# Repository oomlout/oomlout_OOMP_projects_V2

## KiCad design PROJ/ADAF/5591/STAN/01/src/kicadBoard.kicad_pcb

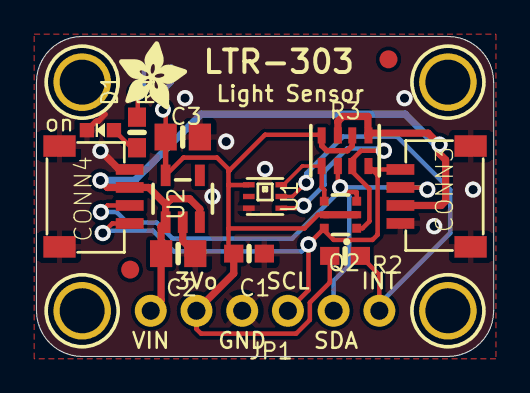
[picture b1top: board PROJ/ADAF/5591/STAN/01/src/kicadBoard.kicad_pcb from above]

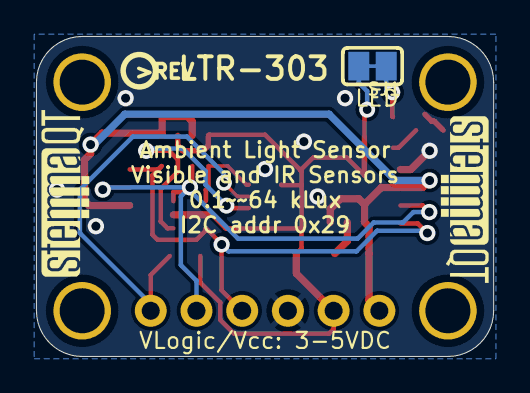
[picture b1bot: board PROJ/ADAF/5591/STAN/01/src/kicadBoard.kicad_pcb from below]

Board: 2 copper layers, 25.4 x 17.8 mm, 24 parts (4 on the bottom side), 10 nets.

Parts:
C1: 0.1uF; 0603-NO
C2, C3: 10uF; 0805-NO
CONN3, CONN4: STEMMA_I2C_QT; JST_SH4
D1: GREEN; CHIPLED_0603_NOOUTLINE
FID3, FID4: FIDUCIAL_1MM
JP1: 1X06_ROUND_70
Q2: BSS138; SOT363
R1, R2: 10K; 0603-NO
R3: 10K Pack; RESPACK_4X0603
SJ1: SOLDERJUMPER_CLOSEDWIRE
U1: LTR_303; LTR390
U2: AP2127K-3.3; SOT23-5
U$1, U$17, U$19, U$21: MOUNTINGHOLE2.5; MOUNTINGHOLE_2.5_PLATED
U$22: ADAFRUIT_3.5MM
U$25: PCBFEAT-REV-040
U$30, U$31: STEMMAQT

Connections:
3.3V: C1.1, C3.1, JP1.2, Q2.2, Q2.5, R2.1, R3.2, R3.4, SJ1.2, U1.1, U2.5
GND: C1.2, C2.2, C3.2, CONN3.1, CONN3.MT1, CONN3.MT2, CONN4.1, CONN4.MT1, CONN4.MT2, D1.C, JP1.3, U1.3, U2.2
INT: JP1.6, R2.2, U1.5
unnamed: D1.A, R1.2
unnamed: R1.1, SJ1.1
SCL: CONN3.4, CONN4.4, JP1.4, Q2.6, R3.8
SCL_3V: Q2.1, R3.7, U1.4
SDA: CONN3.3, CONN4.3, JP1.5, Q2.3, R3.6
SDA_3V: Q2.4, R3.5, U1.6
VCC: C2.1, CONN3.2, CONN4.2, JP1.1, R3.1, R3.3, U2.1, U2.3

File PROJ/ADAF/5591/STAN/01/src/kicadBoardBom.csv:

"Id";"Designator";"Package";"Quantity";"Designation";"Supplier and ref";
1;"JP1";"1X06_ROUND_70";1;"";;;
2;"C1";"0603-NO";1;"0.1uF";;;
3;"C3,C2";"0805-NO";2;"10uF";;;
4;"D1";"CHIPLED_0603_NOOUTLINE";1;"GREEN";;;
5;"FID4,FID3";"FIDUCIAL_1MM";2;"FIDUCIAL_1MM";;;
6;"U2";"SOT23-5";1;"AP2127K-3.3";;;
7;"U$17,U$21,U$1,U$19";"MOUNTINGHOLE_2.5_PLATED";4;"MOUNTINGHOLE2.5";;;
8;"Q2";"SOT363";1;"BSS138";;;
9;"CONN3,CONN4";"JST_SH4";2;"STEMMA_I2C_QT";;;
10;"R2,R1";"0603-NO";2;"10K";;;
11;"R3";"RESPACK_4X0603";1;"10K Pack";;;
12;"U1";"LTR390";1;"LTR_303";;;
13;"U$22";"ADAFRUIT_3.5MM";1;"";;;
14;"U$30,U$31";"STEMMAQT";2;"";;;
15;"U$25";"PCBFEAT-REV-040";1;"";;;
16;"SJ1";"SOLDERJUMPER_CLOSEDWIRE";1;"";;;

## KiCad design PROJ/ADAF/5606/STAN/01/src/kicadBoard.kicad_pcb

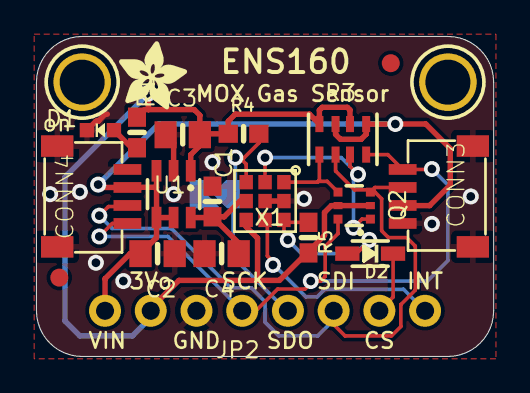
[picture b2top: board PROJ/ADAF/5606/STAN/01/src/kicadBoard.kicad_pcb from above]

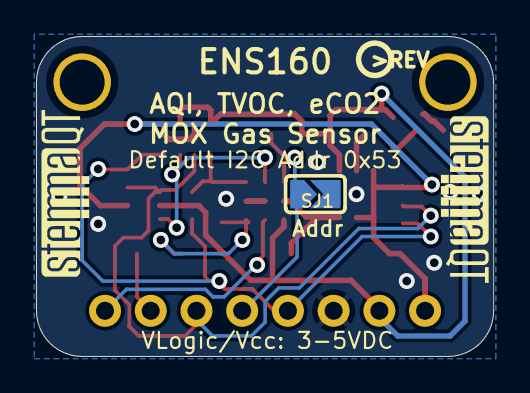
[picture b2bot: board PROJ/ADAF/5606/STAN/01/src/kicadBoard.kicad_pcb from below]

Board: 2 copper layers, 25.4 x 17.8 mm, 25 parts (4 on the bottom side), 13 nets.

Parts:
C1: 0.1uF; 0603-NO
C2, C3, C4: 10uF; 0805-NO
CONN3, CONN4: STEMMA_I2C_QT; JST_SH4
D1: GREEN; CHIPLED_0603_NOOUTLINE
D2: 1N4148; SOD-323
FID3, FID4: FIDUCIAL_1MM
JP2: 1X08_ROUND_70
Q2: BSS138; SOT363
R1, R4, R5: 10K; 0603-NO
R3: 10K pack; RESPACK_4X0603
SJ1: SOLDERJUMPER_ARROW_NOPASTE
U1: AP7312-1833; SOT23-6
U$1, U$17: MOUNTINGHOLE2.5; MOUNTINGHOLE_2.5_PLATED
U$20: ADAFRUIT_3.5MM
U$25: PCBFEAT-REV-040
U$30, U$31: STEMMAQT
X1: ENS160

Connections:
1.8V: C1.1, C4.1, U1.6, X1.4
3.3V: C3.1, JP2.2, Q2.2, Q2.5, R1.1, R3.2, R3.4, R4.2, R5.2, U1.1, X1.5
CS_3V: D2.A, R5.1, X1.7
GND: C1.2, C2.2, C3.2, C4.2, CONN3.1, CONN3.MT1, CONN3.MT2, CONN4.1, CONN4.MT1, CONN4.MT2, D1.C, JP2.3, SJ1.2, U1.2, X1.8, X1.9
unnamed: D1.A, R1.2
SCL/SCK: CONN3.4, CONN4.4, JP2.4, Q2.6, R3.8
SCL_3V: Q2.1, R3.7, X1.2
SDA/MOSI: CONN3.3, CONN4.3, JP2.6, Q2.3, R3.6
SDA_3V: Q2.4, R3.5, X1.1
SDO/ADR: JP2.5, R4.1, SJ1.1, X1.3
VCC: C2.1, CONN3.2, CONN4.2, JP2.1, R3.1, R3.3, U1.3, U1.4, U1.5
~CS: D2.C, JP2.7
~INT: JP2.8, X1.6

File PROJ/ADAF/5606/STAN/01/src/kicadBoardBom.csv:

"Id";"Designator";"Package";"Quantity";"Designation";"Supplier and ref";
1;"CONN3,CONN4";"JST_SH4";2;"STEMMA_I2C_QT";;;
2;"C4,C3,C2";"0805-NO";3;"10uF";;;
3;"R3";"RESPACK_4X0603";1;"10K pack";;;
4;"R4,R1,R5";"0603-NO";3;"10K";;;
5;"FID4,FID3";"FIDUCIAL_1MM";2;"FIDUCIAL_1MM";;;
6;"U1";"SOT23-6";1;"AP7312-1833";;;
7;"X1";"ENS160";1;"ENS160";;;
8;"D2";"SOD-323";1;"1N4148";;;
9;"D1";"CHIPLED_0603_NOOUTLINE";1;"GREEN";;;
10;"U$20";"ADAFRUIT_3.5MM";1;"";;;
11;"Q2";"SOT363";1;"BSS138";;;
12;"JP2";"1X08_ROUND_70";1;"";;;
13;"C1";"0603-NO";1;"0.1uF";;;
14;"U$17,U$1";"MOUNTINGHOLE_2.5_PLATED";2;"MOUNTINGHOLE2.5";;;
15;"U$25";"PCBFEAT-REV-040";1;"";;;
16;"SJ1";"SOLDERJUMPER_ARROW_NOPASTE";1;"";;;
17;"U$30,U$31";"STEMMAQT";2;"";;;

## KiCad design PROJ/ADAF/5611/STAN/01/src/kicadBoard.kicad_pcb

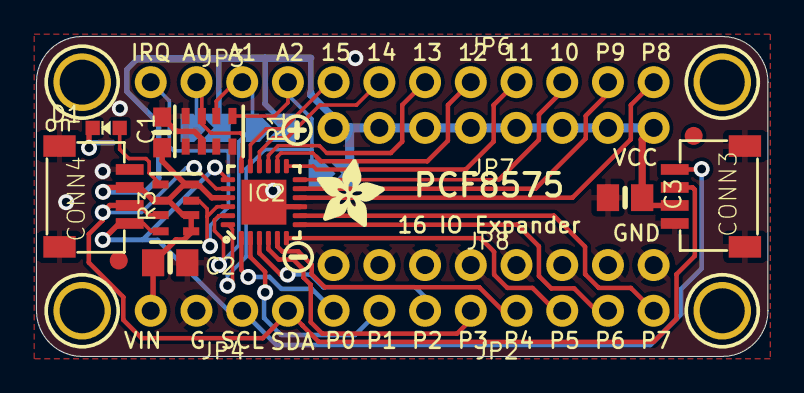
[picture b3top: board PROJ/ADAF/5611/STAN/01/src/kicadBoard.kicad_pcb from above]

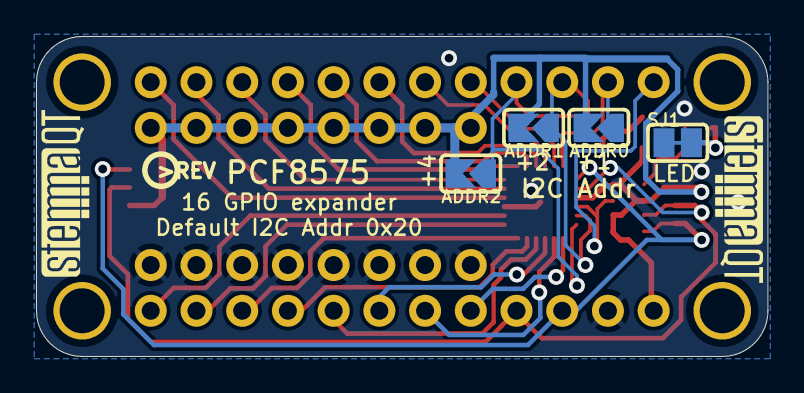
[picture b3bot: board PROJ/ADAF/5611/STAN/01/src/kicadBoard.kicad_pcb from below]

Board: 2 copper layers, 40.6 x 17.8 mm, 31 parts (7 on the bottom side), 26 nets.

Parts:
ADDR0, ADDR1, ADDR2: SOLDERJUMPER_ARROW_NOPASTE
C1: 0.1uF; 0603-NO
C2, C3: 10uF; 0805-NO
CONN3, CONN4: STEMMA_I2C_QT; JST_SH4
D1: GREEN; CHIPLED_0603_NOOUTLINE
FID3, FID4: FIDUCIAL_1MM
IC2: PCF8575; QFN24_4MM_SMSC
JP2, JP6, JP7, JP8: 1X08_ROUND_70
JP3, JP4: 1X04_ROUND
R1, R3: 10K Pack; RESPACK_4X0603
SJ1: SOLDERJUMPER_CLOSEDWIRE
U$1, U$17, U$19, U$21: MOUNTINGHOLE2.5; MOUNTINGHOLE_2.5_PLATED
U$2: SYMBOL_PLUS
U$3: SYMBOL_MINUS
U$22: ADAFRUIT_3.5MM
U$25: PCBFEAT-REV-040
U$30, U$31: STEMMAQT

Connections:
A0: ADDR0.1, IC2.18, JP3.2, R1.7
A1: ADDR1.1, IC2.23, JP3.3, R1.6
A2: ADDR2.1, IC2.24, JP3.4, R1.5
GND: C1.2, C2.2, C3.2, CONN3.1, CONN3.MT1, CONN3.MT2, CONN4.1, CONN4.MT1, CONN4.MT2, IC2.9, IC2.THERM, JP4.2, JP8.1, JP8.2, JP8.3, JP8.4, JP8.5, JP8.6, JP8.7, JP8.8, R1.1, R1.2, R1.3, R1.4, R1.8, SJ1.1
GPA0: IC2.1, JP2.1
GPA1: IC2.2, JP2.2
GPA2: IC2.3, JP2.3
GPA3: IC2.4, JP2.4
GPA4: IC2.5, JP2.5
GPA5: IC2.6, JP2.6
GPA6: IC2.7, JP2.7
GPA7: IC2.8, JP2.8
GPB0: IC2.10, JP6.1
GPB1: IC2.11, JP6.2
GPB2: IC2.12, JP6.3
GPB3: IC2.13, JP6.4
GPB4: IC2.14, JP6.5
GPB5: IC2.15, JP6.6
GPB6: IC2.16, JP6.7
GPB7: IC2.17, JP6.8
INTA: IC2.22, JP3.1, R3.3
unnamed: D1.A, R3.5
unnamed: D1.C, SJ1.2
SCL: CONN3.4, CONN4.4, IC2.19, JP4.3, R3.8
SDA: CONN3.3, CONN4.3, IC2.20, JP4.4, R3.7
VCC: ADDR0.2, ADDR1.2, ADDR2.2, C1.1, C2.1, C3.1, CONN3.2, CONN4.2, IC2.21, JP4.1, JP7.1, JP7.2, JP7.3, JP7.4, JP7.5, JP7.6, JP7.7, JP7.8, R3.1, R3.2, R3.4, R3.6

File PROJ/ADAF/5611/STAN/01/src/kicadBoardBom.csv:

"Id";"Designator";"Package";"Quantity";"Designation";"Supplier and ref";
1;"CONN4,CONN3";"JST_SH4";2;"STEMMA_I2C_QT";;;
2;"IC2";"QFN24_4MM_SMSC";1;"PCF8575";;;
3;"C2,C3";"0805-NO";2;"10uF";;;
4;"JP8,JP6,JP2,JP7";"1X08_ROUND_70";4;"";;;
5;"U$3";"SYMBOL_MINUS";1;"";;;
6;"D1";"CHIPLED_0603_NOOUTLINE";1;"GREEN";;;
7;"FID4,FID3";"FIDUCIAL_1MM";2;"FIDUCIAL_1MM";;;
8;"U$22";"ADAFRUIT_3.5MM";1;"";;;
9;"U$2";"SYMBOL_PLUS";1;"";;;
10;"R3,R1";"RESPACK_4X0603";2;"10K Pack";;;
11;"U$17,U$21,U$19,U$1";"MOUNTINGHOLE_2.5_PLATED";4;"MOUNTINGHOLE2.5";;;
12;"C1";"0603-NO";1;"0.1uF";;;
13;"JP4,JP3";"1X04_ROUND";2;"";;;
14;"U$31,U$30";"STEMMAQT";2;"";;;
15;"ADDR0,ADDR2,ADDR1";"SOLDERJUMPER_ARROW_NOPASTE";3;"";;;
16;"U$25";"PCBFEAT-REV-040";1;"";;;
17;"SJ1";"SOLDERJUMPER_CLOSEDWIRE";1;"";;;

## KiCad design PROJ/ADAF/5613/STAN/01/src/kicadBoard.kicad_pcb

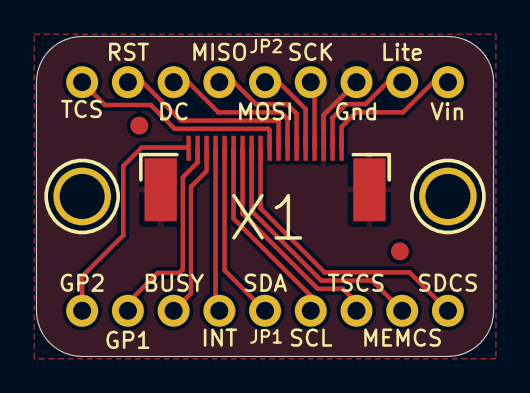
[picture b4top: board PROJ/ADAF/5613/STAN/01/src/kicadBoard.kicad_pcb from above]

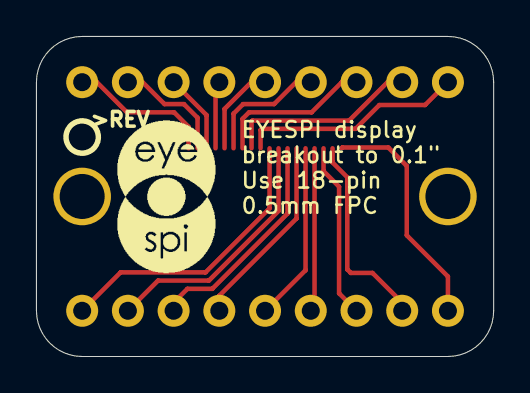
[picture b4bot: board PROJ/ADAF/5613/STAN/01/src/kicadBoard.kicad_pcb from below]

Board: 16 copper layers, 25.4 x 17.8 mm, 9 parts (2 on the bottom side), 18 nets.

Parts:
JP1, JP2: 1X09_ROUND_70
U$2: PCBFEAT-REV-040
U$4, U$5: FIDUCIAL_1MM
U$9, U$10: MOUNTINGHOLE2.5; MOUNTINGHOLE_2.5_PLATED
U$22: EYESPI_MINI_LOGO
X1: EYE_SPI_DISPLAY_FLIP; EYE_SPI_DISPLAY_BOTCONTACT

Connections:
BUSY: JP1.7, X1.16
CARDCS: JP1.1, X1.10
GND: JP2.3, X1.3, X1.SUPPORT1, X1.SUPPORT2
GPIO1: JP1.8, X1.17
GPIO2: JP1.9, X1.18
INT: JP1.6, X1.15
LITE: JP2.2, X1.2
MEM_CS: JP1.2, X1.11
MISO: JP2.6, X1.6
MOSI: JP2.5, X1.5
SCK: JP2.4, X1.4
SCL: JP1.4, X1.13
SDA: JP1.5, X1.14
TFTCS: JP2.9, X1.9
TFTDC: JP2.7, X1.7
TFTRST: JP2.8, X1.8
TSCS: JP1.3, X1.12
VIN: JP2.1, X1.1

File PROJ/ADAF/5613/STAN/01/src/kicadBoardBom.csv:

"Id";"Designator";"Package";"Quantity";"Designation";"Supplier and ref";
1;"U$9,U$10";"MOUNTINGHOLE_2.5_PLATED";2;"MOUNTINGHOLE2.5";;;
2;"U$5,U$4";"FIDUCIAL_1MM";2;"FIDUCIAL_1MM";;;
3;"JP2,JP1";"1X09_ROUND_70";2;"";;;
4;"X1";"EYE_SPI_DISPLAY_BOTCONTACT";1;"EYE_SPI_DISPLAY_FLIP";;;
5;"U$22";"EYESPI_MINI_LOGO";1;"";;;
6;"U$2";"PCBFEAT-REV-040";1;"";;;

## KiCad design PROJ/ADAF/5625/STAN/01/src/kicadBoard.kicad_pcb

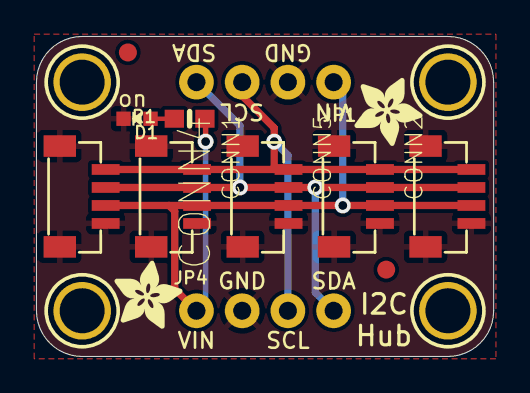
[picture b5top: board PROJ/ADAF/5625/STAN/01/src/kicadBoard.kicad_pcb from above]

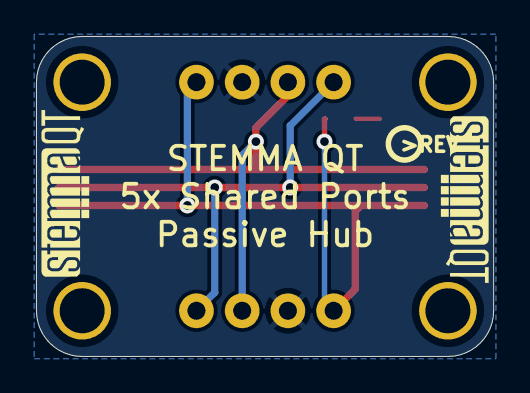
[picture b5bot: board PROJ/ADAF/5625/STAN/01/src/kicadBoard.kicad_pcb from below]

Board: 2 copper layers, 25.4 x 17.8 mm, 20 parts (3 on the bottom side), 5 nets.

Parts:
CONN1, CONN2, CONN3, CONN4, CONN5: STEMMA_I2C_QTRA; JST_SH4_RA
D1: GREEN; CHIPLED_0603_NOOUTLINE
FID3, FID4: FIDUCIAL_1MM
JP1, JP4: 1X04_ROUND_76
R1: 10K; 0603-NO
U$1, U$17, U$19, U$21: MOUNTINGHOLE2.5; MOUNTINGHOLE_2.5_PLATED
U$2, U$3: ADAFRUIT_3.5MM
U$25: PCBFEAT-REV-040
U$30, U$31: STEMMAQT

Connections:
GND: CONN1.1, CONN1.MT1, CONN1.MT2, CONN2.1, CONN2.MT1, CONN2.MT2, CONN3.1, CONN3.MT1, CONN3.MT2, CONN4.1, CONN4.MT1, CONN4.MT2, CONN5.1, CONN5.MT1, CONN5.MT2, D1.C, JP1.2, JP4.2
unnamed: D1.A, R1.2
SCL: CONN1.4, CONN2.4, CONN3.4, CONN4.4, CONN5.4, JP1.3, JP4.3
SDA: CONN1.3, CONN2.3, CONN3.3, CONN4.3, CONN5.3, JP1.4, JP4.4
VCC: CONN1.2, CONN2.2, CONN3.2, CONN4.2, CONN5.2, JP1.1, JP4.1, R1.1

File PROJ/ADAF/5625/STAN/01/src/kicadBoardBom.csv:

"Id";"Designator";"Package";"Quantity";"Designation";"Supplier and ref";
1;"CONN2,CONN3,CONN1,CONN4,CONN5";"JST_SH4_RA";5;"STEMMA_I2C_QTRA";;;
2;"D1";"CHIPLED_0603_NOOUTLINE";1;"GREEN";;;
3;"FID4,FID3";"FIDUCIAL_1MM";2;"FIDUCIAL_1MM";;;
4;"U$17,U$21,U$19,U$1";"MOUNTINGHOLE_2.5_PLATED";4;"MOUNTINGHOLE2.5";;;
5;"U$3,U$2";"ADAFRUIT_3.5MM";2;"";;;
6;"JP1,JP4";"1X04_ROUND_76";2;"";;;
7;"R1";"0603-NO";1;"10K";;;
8;"U$30,U$31";"STEMMAQT";2;"";;;
9;"U$25";"PCBFEAT-REV-040";1;"";;;

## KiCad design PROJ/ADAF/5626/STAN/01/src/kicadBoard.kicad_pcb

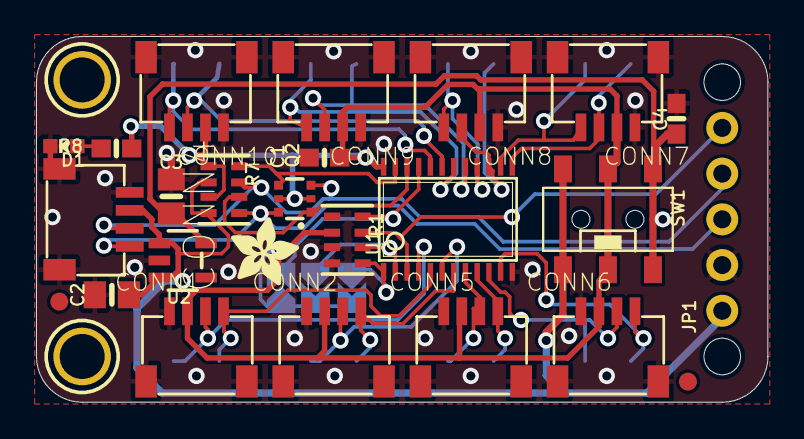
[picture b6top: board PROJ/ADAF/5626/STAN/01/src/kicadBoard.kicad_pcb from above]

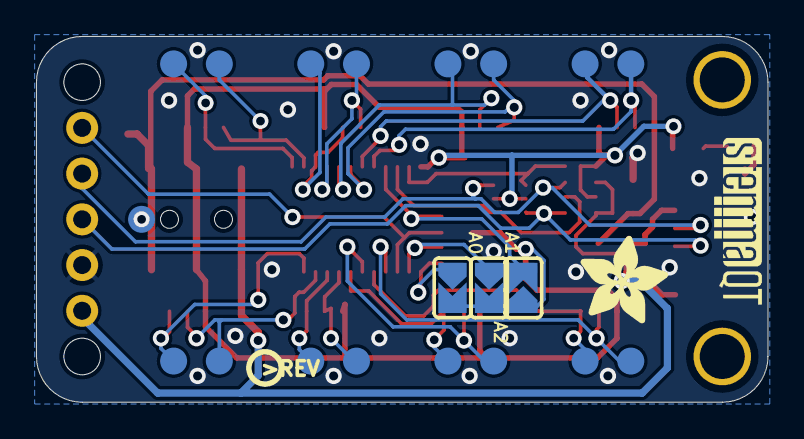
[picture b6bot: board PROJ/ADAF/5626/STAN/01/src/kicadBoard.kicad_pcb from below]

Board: 2 copper layers, 40.6 x 20.3 mm, 77 parts (28 on the bottom side), 29 nets.

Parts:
@HOLE0, @HOLE1: (no value)
A0, A1, A2: SOLDERJUMPER_ARROW_NOPASTE
C1: 1uF; 0603-NO
C2, C3: 10uF; 0805-NO
C4: 0.1uF; 0603-NO
CONN1, CONN2, CONN4, CONN5, CONN6, CONN7, CONN8, CONN9, CONN10: STEMMA_I2C_QT; JST_SH4
D1: GREEN; CHIPLED_0603_NOOUTLINE
FID2, FID4: FIDUCIAL_1MM
JP1: 1X05_ROUND_70
PLABEL0: PLABEL0
PLABEL1: PLABEL1
PLABEL2: PLABEL2
PLABEL3: PLABEL3
PLABEL4: PLABEL4
PLABEL5: PLABEL5
PLABEL6: PLABEL6
PLABEL7: PLABEL7
PLABEL8: PLABEL8
PLABEL9: PLABEL9
PLABEL10: PLABEL10
PLABEL11: PLABEL11
PLABEL12: PLABEL12
PLABEL13: PLABEL13
PLABEL14: PLABEL14
PLABEL15: PLABEL15
PLABEL16: PLABEL16
PLABEL17: PLABEL17
PLABEL18: PLABEL18
PLABEL19: PLABEL19
PLABEL20: PLABEL20
PLABEL21: PLABEL21
PLABEL22: PLABEL22
PLABEL23: PLABEL23
PLABEL24: PLABEL24
Q2: BSS138; SOT363
R1, R7: 10K Pack; RESPACK_4X0603
R8: 10K; 0603-NO
SW1: AYZ0202AGRLC; EG1390
TP1, TP2, TP3, TP4, TP5, TP6, TP7, TP8, TP9, TP10, TP11, TP12, TP13, TP14, TP15, TP16, TP17: TESTPOINT_ROUND_1.5MM_NO
U1: xCA9548APWR; TSSOP24
U2: AP2112K-3.3; SOT23-5
U$5: ADAFRUIT_5MM
U$19, U$22: MOUNTINGHOLE2.5; MOUNTINGHOLE_2.5_PLATED
U$28: ADAFRUIT_3.5MM
U$29: PCBFEAT-REV-040
U$31: STEMMAQT

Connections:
0SCL: CONN1.4, TP15.P$1, U1.5
0SDA: CONN1.3, TP16.P$1, U1.4
1SCL: CONN2.4, TP13.P$1, U1.7
1SDA: CONN2.3, TP14.P$1, U1.6
2SCL: CONN5.4, TP11.P$1, U1.9
2SDA: CONN5.3, TP12.P$1, U1.8
3.3V: C3.1, C4.1, SW1.O1, SW1.O2, TP17.P$1, U2.5
3SCL: CONN6.4, TP9.P$1, U1.11
3SDA: CONN6.3, TP10.P$1, U1.10
4SCL: CONN7.4, TP8.P$1, U1.14
4SDA: CONN7.3, TP7.P$1, U1.13
5SCL: CONN8.4, TP5.P$1, U1.16
5SDA: CONN8.3, TP6.P$1, U1.15
6SCL: CONN9.4, TP3.P$1, U1.18
6SDA: CONN9.3, TP4.P$1, U1.17
7SCL: CONN10.4, TP1.P$1, U1.20
7SDA: CONN10.3, TP2.P$1, U1.19
A0: A0.1, R1.5, U1.1
A1: A1.1, R1.6, U1.2
A2: A2.2, R1.8, U1.21
GND: C1.2, C2.2, C3.2, C4.2, CONN1.1, CONN1.MT1, CONN1.MT2, CONN2.1, CONN2.MT1, CONN2.MT2, CONN4.1, CONN4.MT1, CONN4.MT2, CONN5.1, CONN5.MT1, CONN5.MT2, CONN6.1, CONN6.MT1, CONN6.MT2, CONN7.1, CONN7.MT1, CONN7.MT2, CONN8.1, CONN8.MT1, CONN8.MT2, CONN9.1, CONN9.MT1, CONN9.MT2, CONN10.1, CONN10.MT1, CONN10.MT2, D1.C, JP1.2, R1.1, R1.3, R1.4, U1.12, U2.2
unnamed: D1.A, R8.2
RESET: JP1.5, R1.7, U1.3
SCL: CONN4.4, JP1.3, Q2.6, R7.5
SCL_IO: Q2.1, R7.6, U1.22
SDA: CONN4.3, JP1.4, Q2.3, R7.7
SDA_IO: Q2.4, R7.8, U1.23
VCC: C2.1, CONN4.2, JP1.1, R7.2, R7.4, SW1.S1, SW1.S2, U2.1, U2.3
VCCIO: A0.2, A1.2, A2.1, C1.1, CONN1.2, CONN2.2, CONN5.2, CONN6.2, CONN7.2, CONN8.2, CONN9.2, CONN10.2, Q2.2, Q2.5, R1.2, R7.1, R7.3, R8.1, SW1.P1, SW1.P2, U1.24

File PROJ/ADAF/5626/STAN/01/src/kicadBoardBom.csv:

"Id";"Designator";"Package";"Quantity";"Designation";"Supplier and ref";
1;"PLABEL17";"PLABEL17";1;"";;;
2;"FID2,FID4";"FIDUCIAL_1MM";2;"FIDUCIAL_1MM";;;
3;"CONN5,CONN2,CONN1,CONN9,CONN7,CONN6,CONN8,CONN4,CONN10";"JST_SH4";9;"STEMMA_I2C_QT";;;
4;"U1";"TSSOP24";1;"xCA9548APWR";;;
5;"R1,R7";"RESPACK_4X0603";2;"10K Pack";;;
6;"PLABEL18";"PLABEL18";1;"";;;
7;"PLABEL3";"PLABEL3";1;"";;;
8;"PLABEL1";"PLABEL1";1;"";;;
9;"PLABEL4";"PLABEL4";1;"";;;
10;"C4";"0603-NO";1;"0.1uF";;;
11;"D1";"CHIPLED_0603_NOOUTLINE";1;"GREEN";;;
12;"C2,C3";"0805-NO";2;"10uF";;;
13;"U$22,U$19";"MOUNTINGHOLE_2.5_PLATED";2;"MOUNTINGHOLE2.5";;;
14;"U$28";"ADAFRUIT_3.5MM";1;"";;;
15;"Q2";"SOT363";1;"BSS138";;;
16;"PLABEL10";"PLABEL10";1;"";;;
17;"PLABEL2";"PLABEL2";1;"";;;
18;"PLABEL7";"PLABEL7";1;"";;;
19;"C1";"0603-NO";1;"1uF";;;
20;"PLABEL19";"PLABEL19";1;"";;;
21;"PLABEL11";"PLABEL11";1;"";;;
22;"PLABEL16";"PLABEL16";1;"";;;
23;"@HOLE1,@HOLE0";"";2;"";;;
24;"JP1";"1X05_ROUND_70";1;"";;;
25;"PLABEL14";"PLABEL14";1;"";;;
26;"PLABEL5";"PLABEL5";1;"";;;
27;"U2";"SOT23-5";1;"AP2112K-3.3";;;
28;"PLABEL9";"PLABEL9";1;"";;;
29;"SW1";"EG1390";1;"AYZ0202AGRLC";;;
30;"PLABEL6";"PLABEL6";1;"";;;
31;"PLABEL0";"PLABEL0";1;"";;;
32;"R8";"0603-NO";1;"10K";;;
33;"PLABEL8";"PLABEL8";1;"";;;
34;"PLABEL13";"PLABEL13";1;"";;;
35;"PLABEL15";"PLABEL15";1;"";;;
36;"PLABEL12";"PLABEL12";1;"";;;
37;"TP7,TP4,TP5,TP12,TP15,TP11,TP2,TP14,TP1,TP17,TP13,TP10,TP16,TP9,TP6,TP3,TP8";"TESTPOINT_ROUND_1.5MM_NO";17;"";;;
38;"A2,A1,A0";"SOLDERJUMPER_ARROW_NOPASTE";3;"";;;
39;"PLABEL24";"PLABEL24";1;"";;;
40;"PLABEL21";"PLABEL21";1;"";;;
41;"U$5";"ADAFRUIT_5MM";1;"";;;
42;"PLABEL20";"PLABEL20";1;"";;;
43;"PLABEL22";"PLABEL22";1;"";;;
44;"U$29";"PCBFEAT-REV-040";1;"";;;
45;"U$31";"STEMMAQT";1;"";;;
46;"PLABEL23";"PLABEL23";1;"";;;

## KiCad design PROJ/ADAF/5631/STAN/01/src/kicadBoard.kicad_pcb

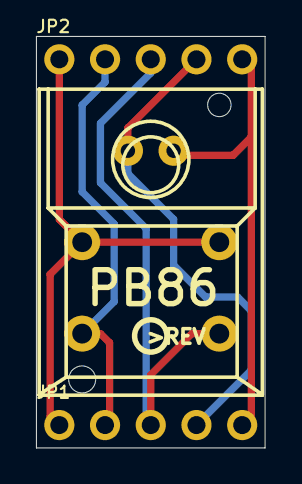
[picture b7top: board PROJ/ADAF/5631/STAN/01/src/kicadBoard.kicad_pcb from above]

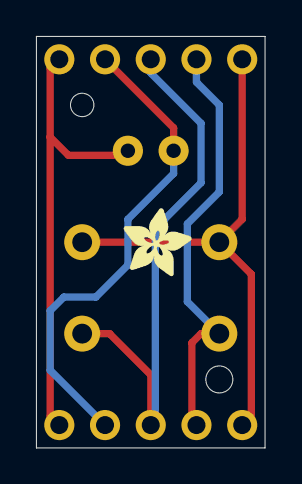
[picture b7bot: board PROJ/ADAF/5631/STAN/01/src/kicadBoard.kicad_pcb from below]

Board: 2 copper layers, 12.7 x 22.9 mm, 25 parts (11 on the bottom side), 5 nets.

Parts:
JP1, JP2: 1X05_ROUND
PLABEL0: PLABEL0
PLABEL1: PLABEL1
PLABEL2: PLABEL2
PLABEL3: PLABEL3
PLABEL4: PLABEL4
PLABEL5: PLABEL5
PLABEL6: PLABEL6
PLABEL7: PLABEL7
PLABEL8: PLABEL8
PLABEL9: PLABEL9
PLABEL10: PLABEL10
PLABEL11: PLABEL11
PLABEL12: PLABEL12
PLABEL13: PLABEL13
PLABEL14: PLABEL14
PLABEL15: PLABEL15
PLABEL16: PLABEL16
PLABEL17: PLABEL17
PLABEL18: PLABEL18
PLABEL19: PLABEL19
SW1: PB86_STEPSWITCH; PB86
U$1: PCBFEAT-REV-040
U$32: ADAFRUIT_3.5MM

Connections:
COM: JP1.1, JP2.1, SW1.1A, SW1.1B
LEDA: JP1.4, JP2.4, SW1.LED+
LEDC: JP1.5, JP2.5, SW1.LED-
NC: JP1.3, JP2.3, SW1.3
NO: JP1.2, JP2.2, SW1.2

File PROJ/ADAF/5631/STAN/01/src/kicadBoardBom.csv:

"Id";"Designator";"Package";"Quantity";"Designation";"Supplier and ref";
1;"PLABEL4";"PLABEL4";1;"";;;
2;"JP1,JP2";"1X05_ROUND";2;"";;;
3;"PLABEL6";"PLABEL6";1;"";;;
4;"PLABEL3";"PLABEL3";1;"";;;
5;"PLABEL0";"PLABEL0";1;"";;;
6;"SW1";"PB86";1;"PB86_STEPSWITCH";;;
7;"PLABEL8";"PLABEL8";1;"";;;
8;"PLABEL2";"PLABEL2";1;"";;;
9;"U$1";"PCBFEAT-REV-040";1;"";;;
10;"PLABEL1";"PLABEL1";1;"";;;
11;"PLABEL5";"PLABEL5";1;"";;;
12;"PLABEL9";"PLABEL9";1;"";;;
13;"PLABEL7";"PLABEL7";1;"";;;
14;"PLABEL13";"PLABEL13";1;"";;;
15;"PLABEL18";"PLABEL18";1;"";;;
16;"PLABEL12";"PLABEL12";1;"";;;
17;"U$32";"ADAFRUIT_3.5MM";1;"";;;
18;"PLABEL10";"PLABEL10";1;"";;;
19;"PLABEL19";"PLABEL19";1;"";;;
20;"PLABEL15";"PLABEL15";1;"";;;
21;"PLABEL11";"PLABEL11";1;"";;;
22;"PLABEL17";"PLABEL17";1;"";;;
23;"PLABEL14";"PLABEL14";1;"";;;
24;"PLABEL16";"PLABEL16";1;"";;;

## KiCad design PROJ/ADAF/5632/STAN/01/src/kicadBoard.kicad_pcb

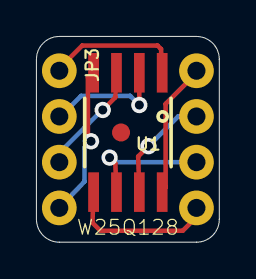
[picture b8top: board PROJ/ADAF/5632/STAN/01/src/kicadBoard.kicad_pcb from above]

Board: 2 copper layers, 10.2 x 11.4 mm, 5 parts (1 on the bottom side), 8 nets.

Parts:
FID1: FIDUCIAL_1MM
JP2, JP3: 1X04_ROUND_76
U1: GENERIC QSPI; SOIC8_208MIL
U$4: ADAFRUIT_2.5MM

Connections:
3.3V: JP2.1, U1.8
GND: JP3.4, U1.4
IO2: JP3.3, U1.3
IO3: JP2.2, U1.7
MISO: JP3.2, U1.2
MOSI: JP2.4, U1.5
SCK: JP2.3, U1.6
SS: JP3.1, U1.1

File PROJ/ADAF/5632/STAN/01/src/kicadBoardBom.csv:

"Id";"Designator";"Package";"Quantity";"Designation";"Supplier and ref";
1;"FID1";"FIDUCIAL_1MM";1;"FIDUCIAL_1MM";;;
2;"U1";"SOIC8_208MIL";1;"GENERIC QSPI";;;
3;"JP3,JP2";"1X04_ROUND_76";2;"";;;
4;"U$4";"ADAFRUIT_2.5MM";1;"";;;
